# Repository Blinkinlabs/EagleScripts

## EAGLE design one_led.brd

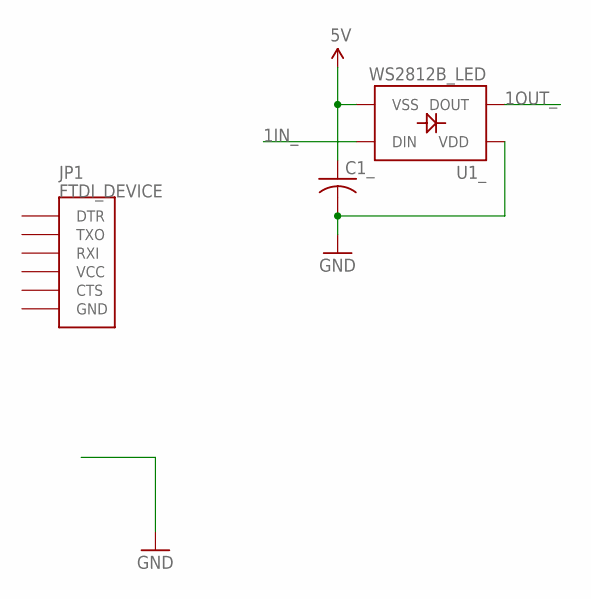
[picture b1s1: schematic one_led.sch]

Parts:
C1_: C-USC0603K; C0603K
JP1: FTDI_DEVICE; FTDI_DEVICE_SIDE
U1_: WS2812B_LED

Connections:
1IN_: U1_.DIN
1OUT_: U1_.DOUT
5V: C1_.1, U1_.VSS
GND: C1_.2, U1_.VDD

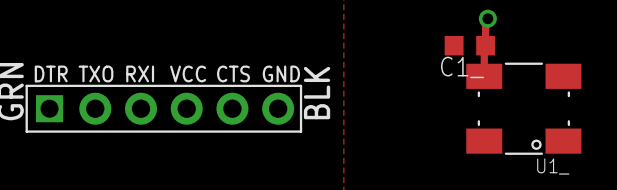
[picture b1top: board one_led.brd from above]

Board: 2 copper layers, 3 parts (0 on the bottom side), 2 nets.

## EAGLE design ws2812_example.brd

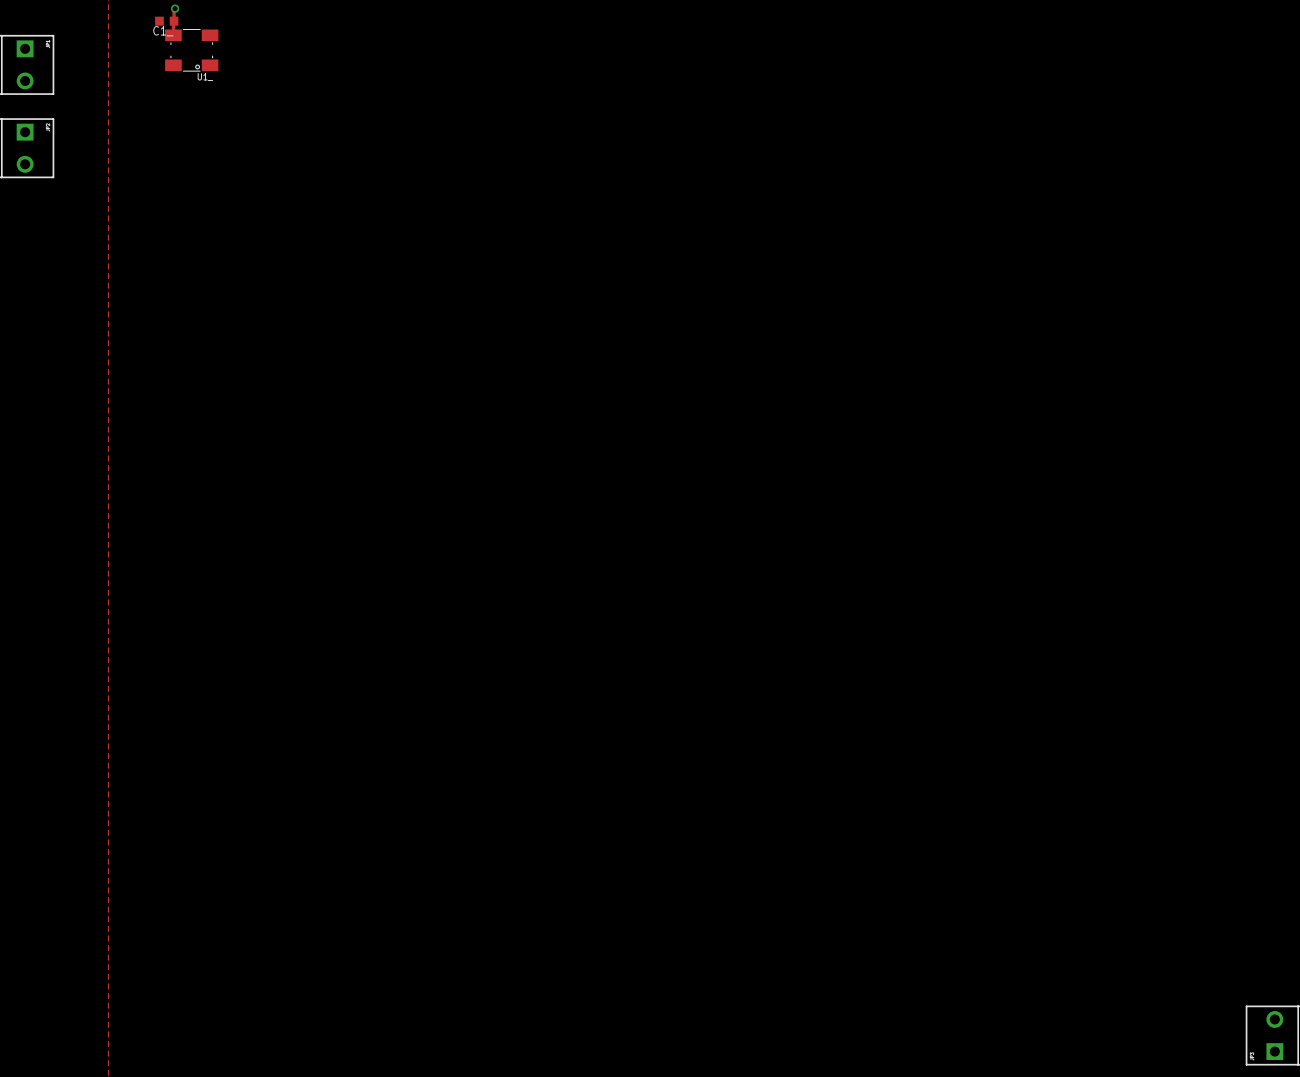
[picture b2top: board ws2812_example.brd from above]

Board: 2 copper layers, 5 parts (0 on the bottom side), 2 nets.

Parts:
C1_: C0603K
JP1, JP3: DATA_IN; SCREWTERMINAL-3.5MM-2_LOCK
JP2: POWER; SCREWTERMINAL-3.5MM-2_LOCK
U1_: WS2812B_LED

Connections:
5V: C1_.1, JP2.2, U1_.VSS
GND: C1_.2, JP1.1, JP2.1, JP3.1, U1_.VDD

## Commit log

2014-02-12 First commit: Eagle array maker
2014-02-15 Add argument variables, do some clean up and consolidation.
2014-02-15 Change whitespace to 4 spaces, add more comments
2014-02-15 Bugfix: Automatically connect array inputs and outputs to any non-array parts that reference them.
2014-02-15 Rename example to reflect it's contents
2014-02-15 Add LED example, row and column matrix builder.
2014-02-16 Add copy group function (to copy wires and vias in the board layout)

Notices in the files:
parts and their libraries:
SparkFun-Connectors: Licensing: CC v3.0 Share-Alike You are welcome to use this library for commercial purposes.
